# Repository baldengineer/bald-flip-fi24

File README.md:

Combination of WiFi (ESP32-S2-WROVER) and nRF24 module on a single Flipper Zero board.

ESP32 / WiFi design based on the Flipper WiFi Development board.

(Work in progress)

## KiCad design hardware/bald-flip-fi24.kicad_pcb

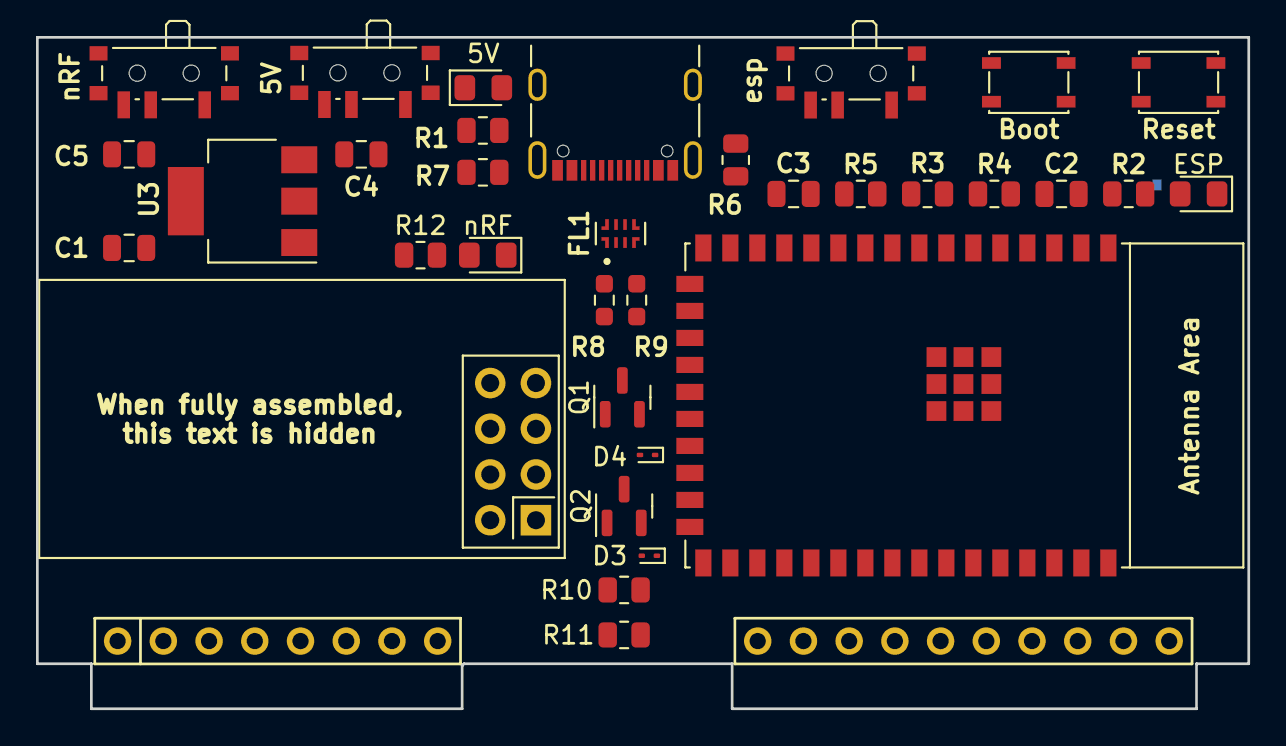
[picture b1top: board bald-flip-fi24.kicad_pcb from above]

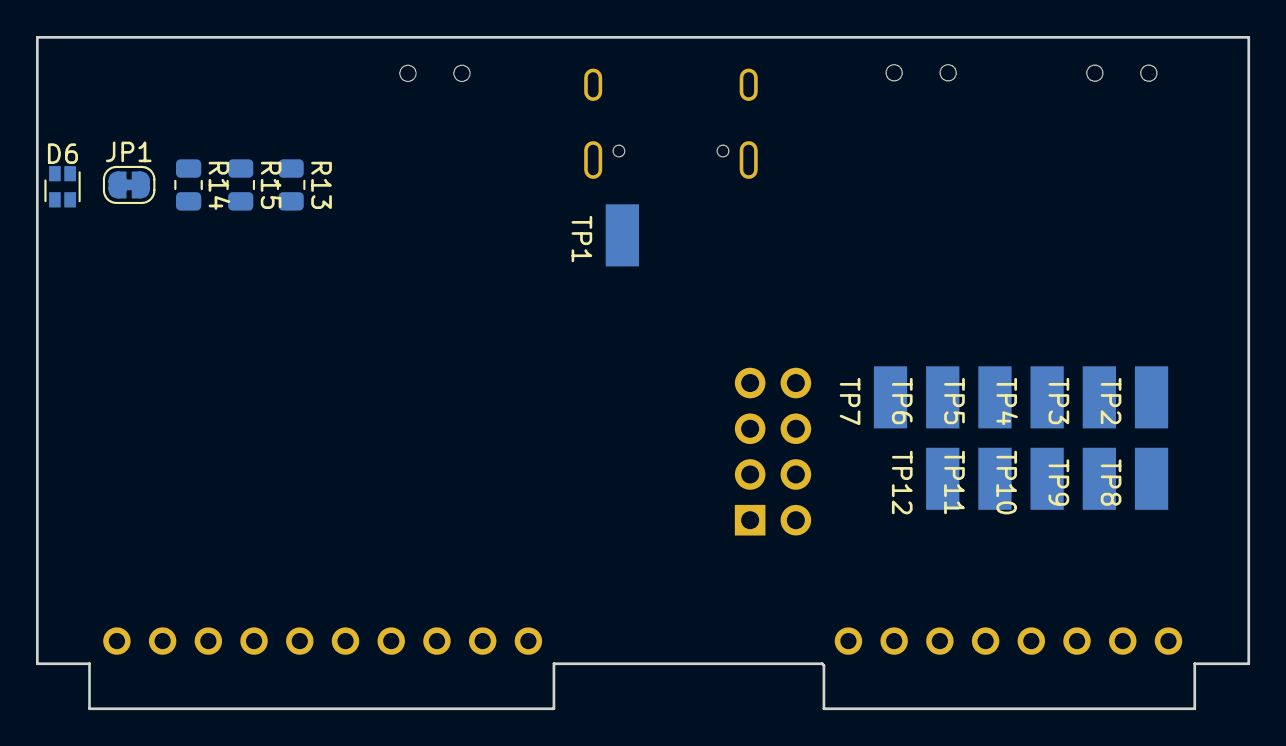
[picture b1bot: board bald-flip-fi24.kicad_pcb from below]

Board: 4 copper layers, 67.3 x 37.3 mm, 53 parts (18 on the bottom side), 39 nets, no tracks yet.

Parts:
C1, C2, C4: 10u; C_0805_2012Metric
C3, C5: 1u; C_0805_2012Metric
D1: 5V; LED_0805_2012Metric_Pad1.15x1.40mm_HandSolder
D2: ESP; LED_0805_2012Metric_Pad1.15x1.40mm_HandSolder
D3, D4: ESD3V3D9-TP; D_SOD-923
D5: nRF; LED_0805_2012Metric_Pad1.15x1.40mm_HandSolder
D6: LTST-C19HE1WT; LED_LiteOn_LTST-C19HE1WT
FL1: ECMF02-4CMX8; FIL_ECMF02-4CMX8
J1: Flipper Header; FlipperZero
J2: USB4105-GF-A; USB_C_Receptacle_GCT_USB4105-xx-A_16P_TopMnt_Horizontal
J3: Flipper Board Outline (Large); Flipper_Board_Outline_baldee
JP1: Jumper_2_Bridged; SolderJumper-2_P1.3mm_Bridged_RoundedPad1.0x1.5mm
Q1, Q2: DMN2058U; SOT-23
R1, R2, R12: 4k7; R_0805_2012Metric
R3, R4, R5: 10k; R_0805_2012Metric
R6, R7: 5k1; R_0805_2012Metric
R8, R9: 22; R_0603_1608Metric_Pad0.98x0.95mm_HandSolder
R10, R11: 150; R_0805_2012Metric
R13, R14: 1k; R_0805_2012Metric
R15: 5.1k; R_0805_2012Metric
SW1: 5V; SW_SPDT_PCM12
SW2: nRF; SW_SPDT_PCM12
SW3: Boot; SW_SPST_PTS810
SW4: Reset; SW_SPST_PTS810
SW5: esp; SW_SPDT_PCM12
TP1, TP2, TP3, TP4, TP5, TP6, TP7, TP8, TP9, TP10, TP11, TP12: TestPoint_Harwin; Harwin-S1751-46-Test-Point
U1: ESP32-S2-WROVER
U2: nRF24; nRF24L01_Breakout
U3: AZ1117IH-3.3TRG1; SOT-223

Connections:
+3V3: C1.1, R3.1, SW2.3 (C), SW5.3 (C), TP11.1, U3.2 (VO), U3.4 (VO)
+5V: C4.1, R1.1, SW1.2 (B), TP8.1, U3.3 (VI)
/A4: J1.4, TP6.1, U1.15 (GPIO12/ADC2_CH1), U2.5 (SCK)
/A6: J1.3, TP7.1, U1.16 (GPIO13/ADC2_CH2), U2.7 (MISO)
/A7: J1.2, TP5.1, U1.14 (GPIO11/ADC2_CH0), U2.6 (MOSI)
/B2: D4.2 (A2), J1.6, Q1.2 (S), R11.2
/B3: J1.5, TP4.1, TP12.1, U1.13 (GPIO10/ADC1_CH9), U2.4 (~CSN)
/Blu: R13.2, U1.7 (GPIO4/ADC1_CH3)
/C3: D3.2 (A2), J1.7, Q2.2 (S), R10.2
/En_ESP: C3.1, Q1.3 (D), R3.2, R5.2, SW4.1, U1.41 (CHIP/PU/RESET)
/Flip_5V: J1.1, SW1.3 (C), TP9.1
/Flip_RX: J1.14, U1.37 (GPIO43/U0TXD/PROG)
/Flip_TX: J1.13, U1.38 (GPIO44/U0RXD/PROG)
/GPIO_0: Q2.3 (D), R4.2, SW3.1, TP2.1, U1.3 (GPIO0/BOOT)
/Grn: R14.2, U1.8 (GPIO5/ADC1_CH4)
/I2C_PU: TP3.1, U1.6 (GPIO3/ADC1_CH2)
/Red: R15.2, U1.9 (GPIO6/ADC1_CH5)
/VBUS: FL1.1 (VBUS), J2.A4 (VBUS), J2.A9 (VBUS), J2.B4 (VBUS), J2.B9 (VBUS), SW1.1 (A)
/esp_VCC: C2.1, R2.1, R4.1, R5.1, SW5.2 (B), U1.2 (3V3)
/esp_d+: FL1.2 (D-_2), R8.2
/esp_d-: FL1.3 (D+_3), R9.2
/nRF_VCC: C5.1, JP1.2 (B), R12.1, SW2.2 (B), TP10.1, U2.2 (VCC)
/usb_d+: FL1.7 (D-_7), J2.A6 (D+), J2.B6 (D+)
/usb_d-: FL1.6 (D+_6), J2.A7 (D-), J2.B7 (D-)
GND: C1.2, C2.2, C3.2, C4.2, C5.2, D1.1 (K), D2.1 (K), D3.1 (A1), D4.1 (A1), D5.1 (K), FL1.5 (GND_5), FL1.8 (GND_8), J1.8, J1.11, J1.18, J2.A1 (GND), J2.A12 (GND), J2.B1 (GND), J2.B12 (GND), J2.S1 (SHIELD), R6.2, R7.2, SW3.2, SW4.2, U1.1 (GND), U1.26 (GND), U1.42 (GND), U1.43 (GND), U2.1 (GND), U3.1 (GND)
unnamed: D1.2 (A), R1.2
unnamed: D2.2 (A), R2.2
unnamed: D5.2 (A), R12.2
unnamed: D6.4 (A), JP1.1 (A)
unnamed: D6.3 (BK), R13.1
unnamed: D6.2 (GK), R14.1
unnamed: D6.1 (RK), R15.1
unnamed: FL1.4 (ID), TP1.1
unnamed: J2.A5 (CC1), R6.1
unnamed: J2.B5 (CC2), R7.1
unnamed: Q1.1 (G), R10.1
unnamed: Q2.1 (G), R11.1
unnamed: R8.1, U1.23 (USB_D+/ADC2_CH9/GPIO20)
unnamed: R9.1, U1.22 (USB_D-/ADC2_CH8/GPIO19)

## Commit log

2023-07-17 initial commit but well into first pcb floorplan
2023-07-17 moved nrf24 to front, I like it better
2023-07-17 re-worked SPi signals, need to consider if firmware can handle moving CS. Cleaned up some silk (for now).
2023-07-18 added RGB and test points
